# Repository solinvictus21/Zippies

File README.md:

# Zippies

Zippies are a project developed to create tiny, open source robots capable of following predefined path routines at high velocity in tight coordination together.

This repository includes all the details you need to build and run a Zippy...

- A complete set of [3D models](BodyModels) created in [SketchUp](https://www.sketchup.com/) that are required to build the outer body of a Zippy. Each of these parts is intended to be printed on a 3D printer and has been exported to a set of [STL files](BodyModels/STL) for convenience.
- A [schematic](LighthouseCircuit) and [complete bill of materials]() for a circuit designed to sense IR signals from a single HTC Vive Lighthouse to enable highly accurate, sub-millimeter localized positioning and orientation. The circuit is built in [AutoDesk Eagle](https://www.autodesk.com/products/eagle/free-download) and the PCB is available for immediate purchase directly [from Osh Park]().
- A complete [list of the additional hardware required](Documentation/Hardware.md) to assemble a Zippy. 
- The [software](PlatformIO) required to enable your Zippy robot to follow any predefined path you wish to create. A sample path is included in the codebase for testing new Zippy builds.
- An [iPhone app](iOSClient) (work in progress) that will allow you to control the Zippy directly and aid in debugging over Bluetooth.
- A [path building app](Builder) (work in progress) using [Unity 3D]() designed to allow you to build and simulate routines for your Zippies to follow and, on supported platforms, allow you to upload them directly to the Zippy via Bluetooth LE for immediate testing.

See each of the links above for more details about each aspect of this project and feel free to contact me for any assistance you may need if you are interested in building your own Zippy.

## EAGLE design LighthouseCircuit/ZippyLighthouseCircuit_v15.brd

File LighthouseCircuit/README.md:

# Lighthouse Sensor Circuit

This circuit is designed to provide sensors that detect IR signals from the HTC Vive Lighthouse in order to provide localized positioning for the Zippy. The board layout is published on [Osh Park](https://oshpark.com/shared_projects/vZVPRIY6) for easy ordering. All you have to do is solder the components onto it. The BOM and links to Digikey components are provided below.

1. 2x [BP104-FASZ](https://www.digikey.com/product-detail/en/osram-opto-semiconductors-inc/BP-104-FAS-Z/475-1344-1-ND/1227850) These are the IR sensors, the eyes of the circuit
2. 1x [TLV2464ID](https://www.digikey.com/product-detail/en/texas-instruments/TLV2464ID/296-10608-5-ND/380874) The heart of the circuit: a fast and reliable quad op-amp from TI.
3. First phase: voltage divider.
  - 2x [27k resistors](https://www.digikey.com/product-detail/en/panasonic-electronic-components/ERJ-3EKF2702V/P27.0KHCT-ND/1746753)
  - 2x [100nF capacictors](https://www.digikey.com/product-detail/en/samsung-electro-mechanics/CL10B104JB8NNNC/1276-1033-1-ND/3889119)
4. Second phase: transimpedance amplification
  - 2x [2.2pF capacitcors](https://www.digikey.com/product-detail/en/samsung-electro-mechanics/CL10C2R2BB8NNNC/1276-1084-1-ND/3889170)
  - 4x [100k resistors](https://www.digikey.com/product-detail/en/panasonic-electronic-components/ERJ-PA3J104V/P100KBZCT-ND/5036238) Also used in fourth-phase inverting amplification.
5. Third phase: high-pass filter.
  - 2x [4.7nf capacitors](https://www.digikey.com/product-detail/en/samsung-electro-mechanics/CL10B472JB8NNNC/1276-2061-1-ND/3890147)
  - 2x [18k resistors](https://www.digikey.com/product-detail/en/panasonic-electronic-components/ERJ-3EKF1802V/P18.0KHCT-ND/1746738)
6. Fourth phase: inverting amplification
  - 2x [1k resistors](https://www.digikey.com/product-detail/en/panasonic-electronic-components/ERJ-PB3D1001V/P20283CT-ND/6214538)

The passives can be soldered onto the board in any orientation, but pay particular attention to the orientation of the op-amp and diodes. Schematic diagram follows below if you're not an Eagle user.

This is essentially a mash-up and a doubling of the circuit I originally started with from [Alex Shtuchkin's project](https://github.com/ashtuchkin/vive-diy-position-sensor) and [another circuit](https://trmm.net/Lighthouse) tweeted about by Alan Yates along with [some lessons I've learned about op-amps](http://www.radio-electronics.com/info/circuits/opamp_non_inverting/op_amp_non-inverting.php) along the way and a LOT of experimentation. At this point, the circuit seems to be fairly reliable across the range of distances that I experiment with.

For the curious, it has been suggested that, if you only have one Lighthouse, you must have three sensors to determine orientation along a 2D plane. Not true, actually. To do it with only two sensors, all you need to know is which sensor was hit first, which is exactly how this project determines orientation along the ground with only two sensors.

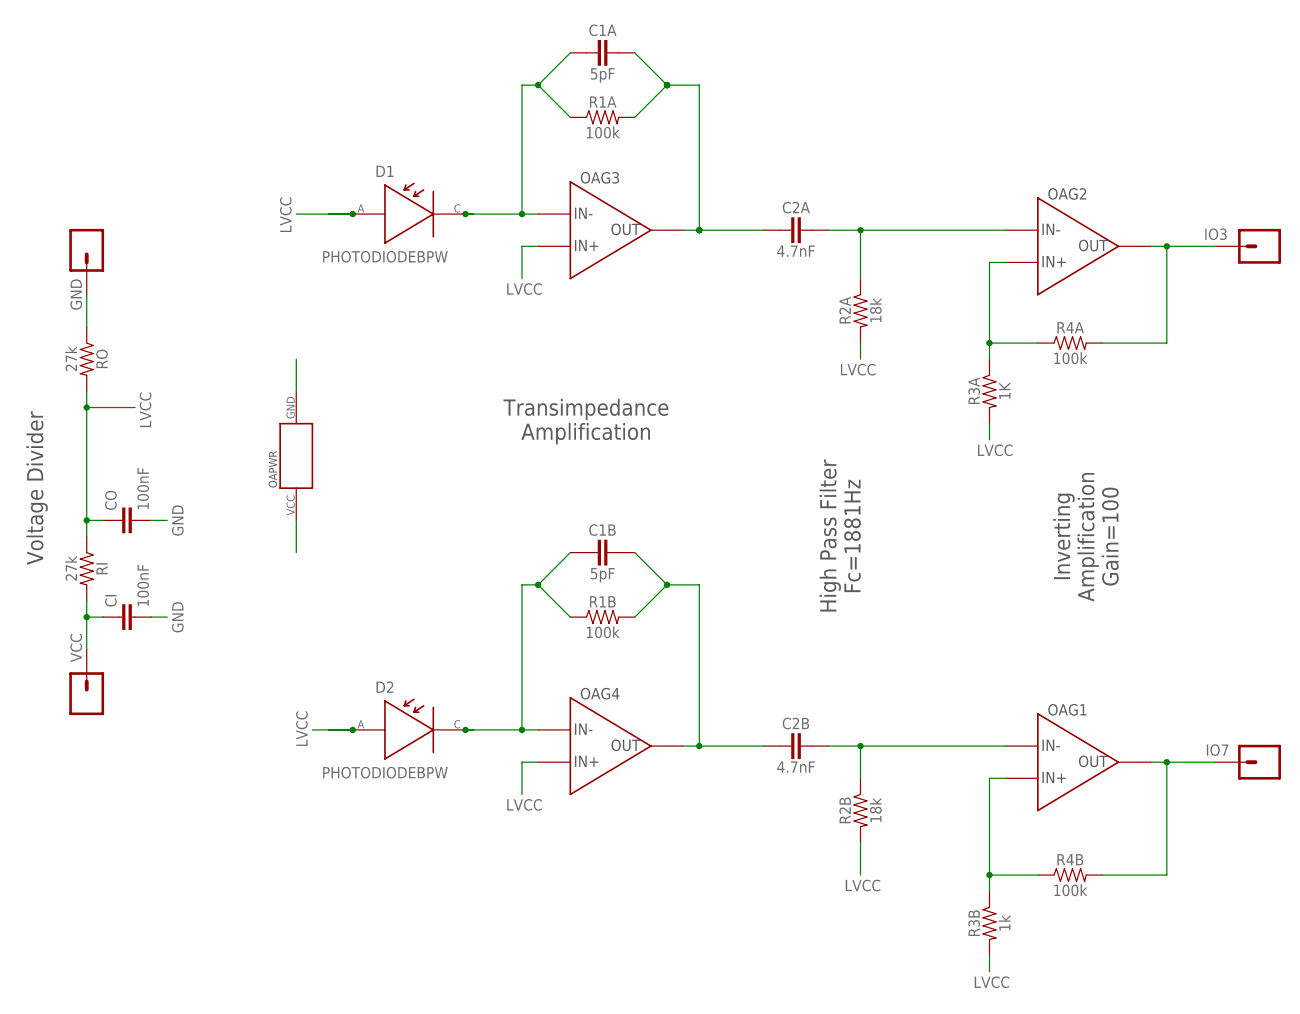
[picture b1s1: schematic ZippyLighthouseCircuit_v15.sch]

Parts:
C1A, C1B: 5pF; PASSIVE-0603
C2A, C2B: 4.7nF; PASSIVE-0603
CI: 100nF; 0603
CO: 100nF; 0603
D1, D2: PHOTODIODEBPW; BPW34_BP104_SMD
GND: CONN_01PTH_NO_SILK_YES_STOP; 1X01_NO_SILK
IO3, IO7: CONN_01PTH_NO_SILK_YES_STOP; 1X01_NO_SILK
OA: TLV2464IDM; D14-M
R1A, R1B, R4A, R4B: 100k; PASSIVE-0603
R2A, R2B: 18k; PASSIVE-0603
R3A: 1K; PASSIVE-0603
R3B: 1k; PASSIVE-0603
RI: 27k; 0603
RO: 27k; 0603
VCC: CONN_01PTH_NO_SILK_YES_STOP; 1X01_NO_SILK

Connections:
D1IN: C1B.1, D2.CATHODE, OA.13 (IN-), R1B.1
D1OA2P: C2B.2, OA.2 (IN-), R2B.1
D1OAOUT1: C1B.2, C2B.1, OA.14 (OUT), R1B.2
D2IN: C1A.1, D1.CATHODE, OA.9 (IN-), R1A.1
D2OA1OUT: C1A.2, C2A.1, OA.8 (OUT), R1A.2
D2OA2N: OA.5 (IN+), R3A.1, R4A.1
D2OA2P: C2A.2, OA.6 (IN-), R2A.1
GND: CI.2, CO.2, GND.1, OA.11 (GND), RO.1
IO3: IO3.1, OA.7 (OUT), R4A.2
IO7: IO7.1, OA.1 (OUT), R4B.2
LVCC: CO.1, D1.ANODE, D2.ANODE, OA.10 (IN+), OA.12 (IN+), R2A.2, R2B.2, R3A.2, R3B.2, RI.1, RO.2
unnamed: OA.3 (IN+), R3B.1, R4B.1
VCC: CI.1, OA.4 (VCC), RI.2, VCC.1

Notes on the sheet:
Voltage Divider
High Pass Filter Fc=1881Hz
Transimpedance Amplification
Inverting Amplification Gain=100

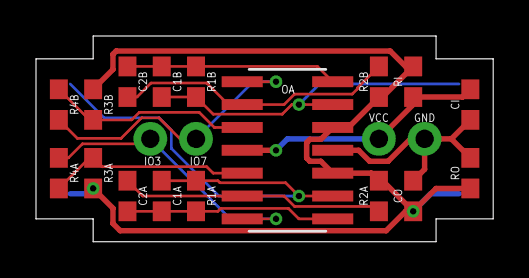
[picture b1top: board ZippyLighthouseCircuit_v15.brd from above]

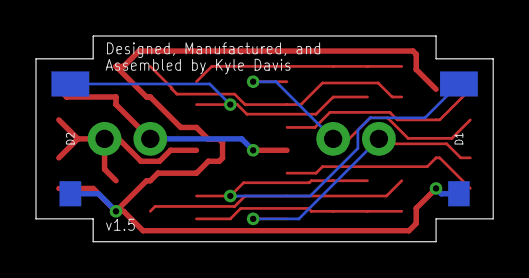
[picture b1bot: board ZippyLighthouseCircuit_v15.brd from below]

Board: 2 copper layers, 25.4 x 11.4 mm, 23 parts (2 on the bottom side), 13 nets.

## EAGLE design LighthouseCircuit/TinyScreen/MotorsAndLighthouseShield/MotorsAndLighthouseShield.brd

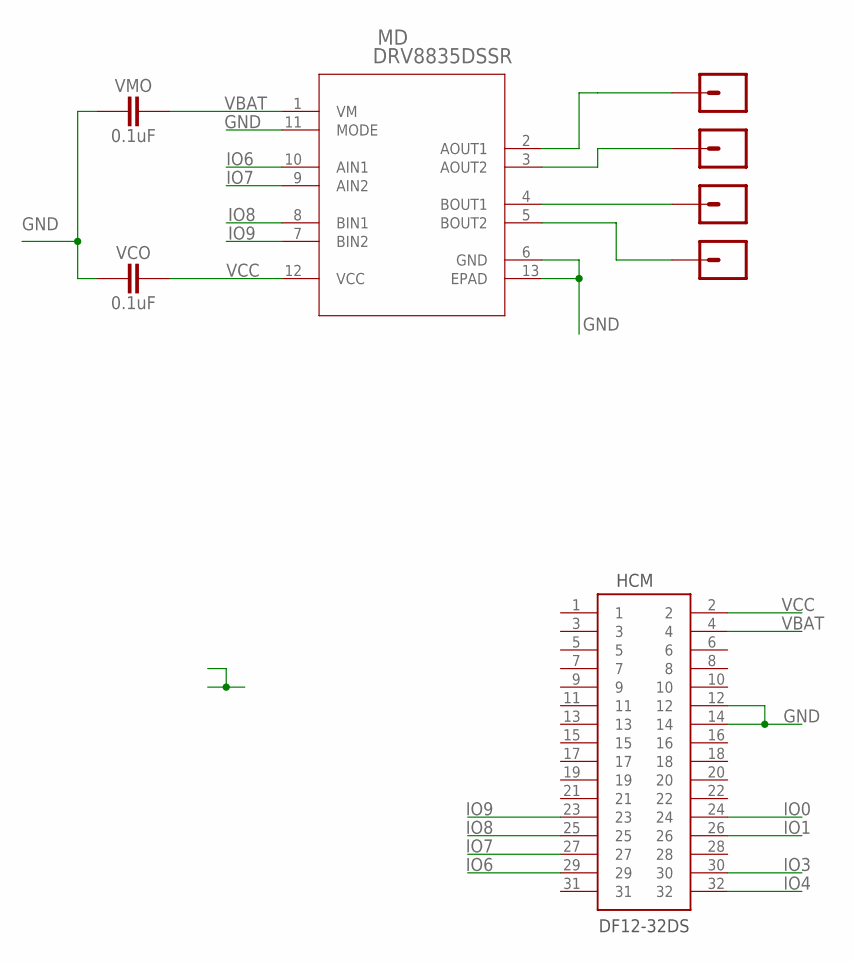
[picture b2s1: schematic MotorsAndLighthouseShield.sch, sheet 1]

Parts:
AO1, AO2: SINGLE-THROUGH-HOLE
B02: SINGLE-THROUGH-HOLE
BO1: SINGLE-THROUGH-HOLE
HCM: HIROSE-DF12-32DSMALE; DF12(3.0)-32DS-0.5V(86)-MALE
MD: DRV8835DSSR; DSS12_P9X2
VCO: 0.1uF; PASSIVE-0603
VMO: 0.1uF; PASSIVE-0603

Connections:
GND: HCM.12, HCM.14, MD.6 (GND), MD.11 (MODE), MD.13 (EPAD), VCO.1, VMO.1; also elsewhere on the board
IO0: HCM.24; also elsewhere on the board
IO1: HCM.26; also elsewhere on the board
IO3: HCM.30
IO4: HCM.32
IO6: HCM.29, MD.10 (AIN1)
IO7: HCM.27, MD.9 (AIN2)
IO8: HCM.25, MD.8 (BIN1)
IO9: HCM.23, MD.7 (BIN2)
unnamed: BO1.1, MD.2 (AOUT1)
unnamed: B02.1, MD.3 (AOUT2)
unnamed: AO1.1, MD.4 (BOUT1)
unnamed: AO2.1, MD.5 (BOUT2)
VBAT: HCM.4, MD.1 (VM), VMO.2
VCC: HCM.2, MD.12 (VCC), VCO.2; also elsewhere on the board

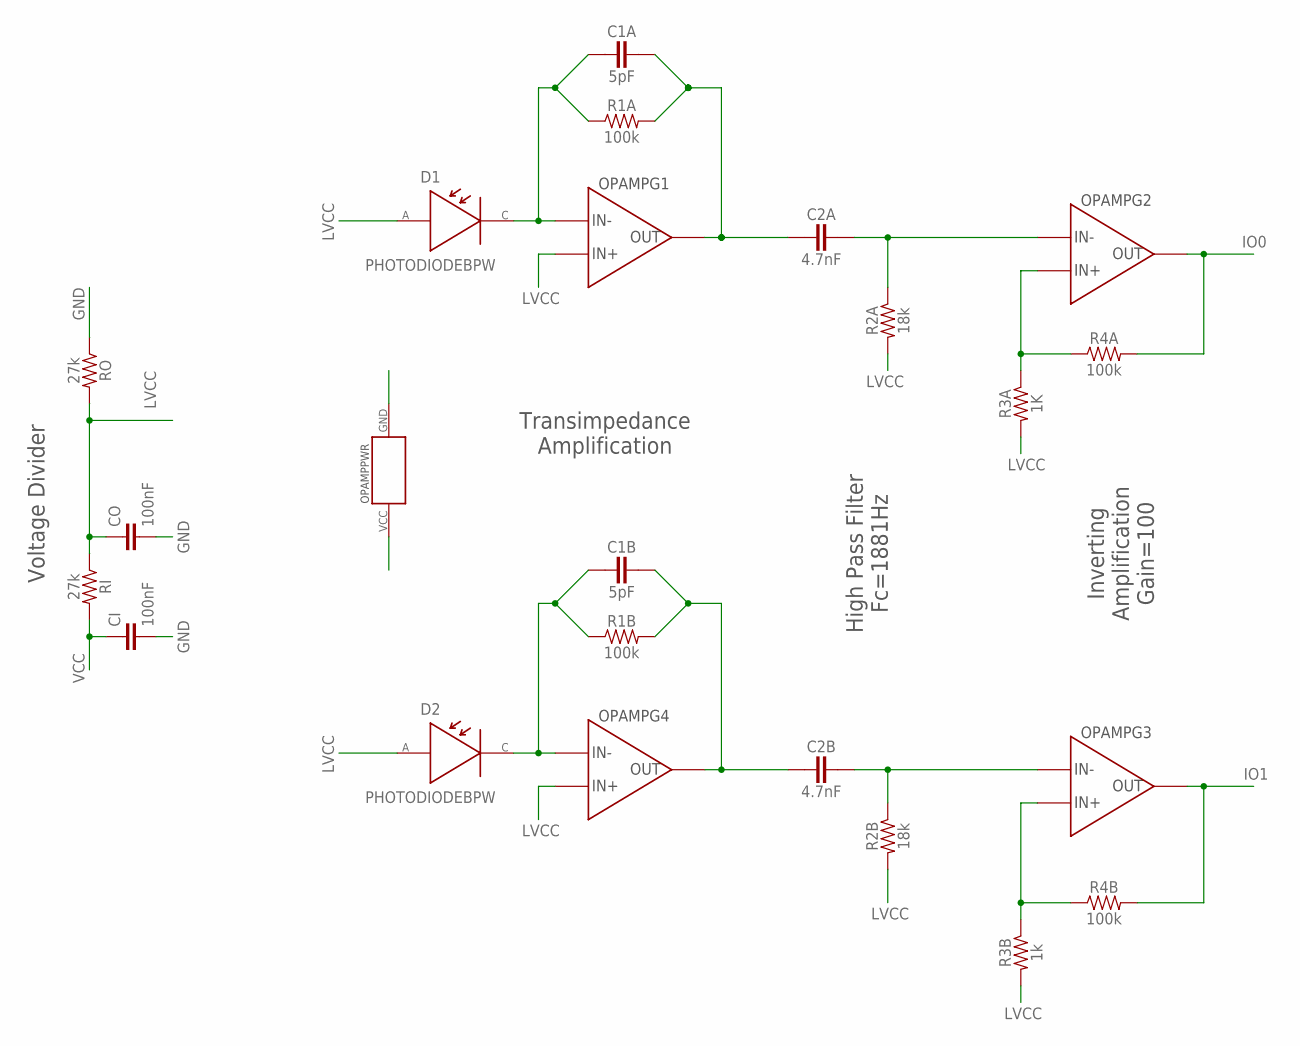
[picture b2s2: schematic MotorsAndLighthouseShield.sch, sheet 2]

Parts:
C1A, C1B: 5pF; PASSIVE-0603
C2A, C2B: 4.7nF; PASSIVE-0603
CI: 100nF; 0603
CO: 100nF; 0603
D1, D2: PHOTODIODEBPW; BPW34_BP104_SMD
OPAMP: TLV2464IPW; PW14
R1A, R1B, R4A, R4B: 100k; PASSIVE-0603
R2A, R2B: 18k; PASSIVE-0603
R3A: 1K; PASSIVE-0603
R3B: 1k; PASSIVE-0603
RI: 27k; 0603
RO: 27k; 0603

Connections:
D1IN1: C1B.1, D2.CATHODE, OPAMP.13 (IN-), R1B.1
D1OA2P1: C2B.2, OPAMP.9 (IN-), R2B.1
D1OAOUT2: C1B.2, C2B.1, OPAMP.14 (OUT), R1B.2
D2IN1: C1A.1, D1.CATHODE, OPAMP.2 (IN-), R1A.1
D2OA1OUT1: C1A.2, C2A.1, OPAMP.1 (OUT), R1A.2
D2OA2N1: OPAMP.5 (IN+), R3A.1, R4A.1
D2OA2P1: C2A.2, OPAMP.6 (IN-), R2A.1
GND: CI.2, CO.2, OPAMP.11 (GND), RO.1; also elsewhere on the board
IO0: OPAMP.7 (OUT), R4A.2; also elsewhere on the board
IO1: OPAMP.8 (OUT), R4B.2; also elsewhere on the board
LVCC: CO.1, D1.ANODE, D2.ANODE, OPAMP.3 (IN+), OPAMP.12 (IN+), R2A.2, R2B.2, R3A.2, R3B.2, RI.1, RO.2
unnamed: OPAMP.10 (IN+), R3B.1, R4B.1
VCC: CI.1, OPAMP.4 (VCC), RI.2; also elsewhere on the board

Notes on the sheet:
Voltage Divider
High Pass Filter Fc=1881Hz
Transimpedance Amplification
Inverting Amplification Gain=100

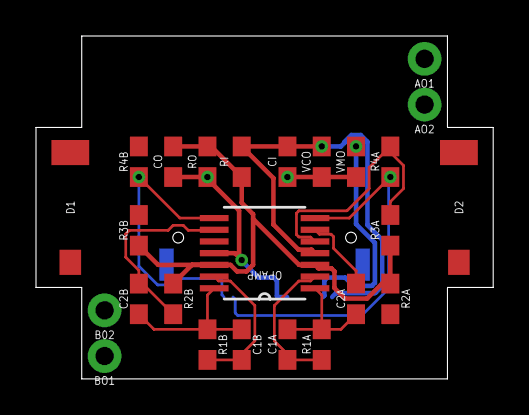
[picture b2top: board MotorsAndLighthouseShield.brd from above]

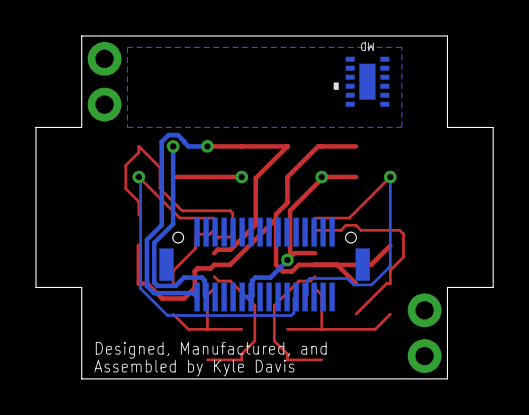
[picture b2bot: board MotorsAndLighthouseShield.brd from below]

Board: 2 copper layers, 25.4 x 19.1 mm, 27 parts (2 on the bottom side), 22 nets.

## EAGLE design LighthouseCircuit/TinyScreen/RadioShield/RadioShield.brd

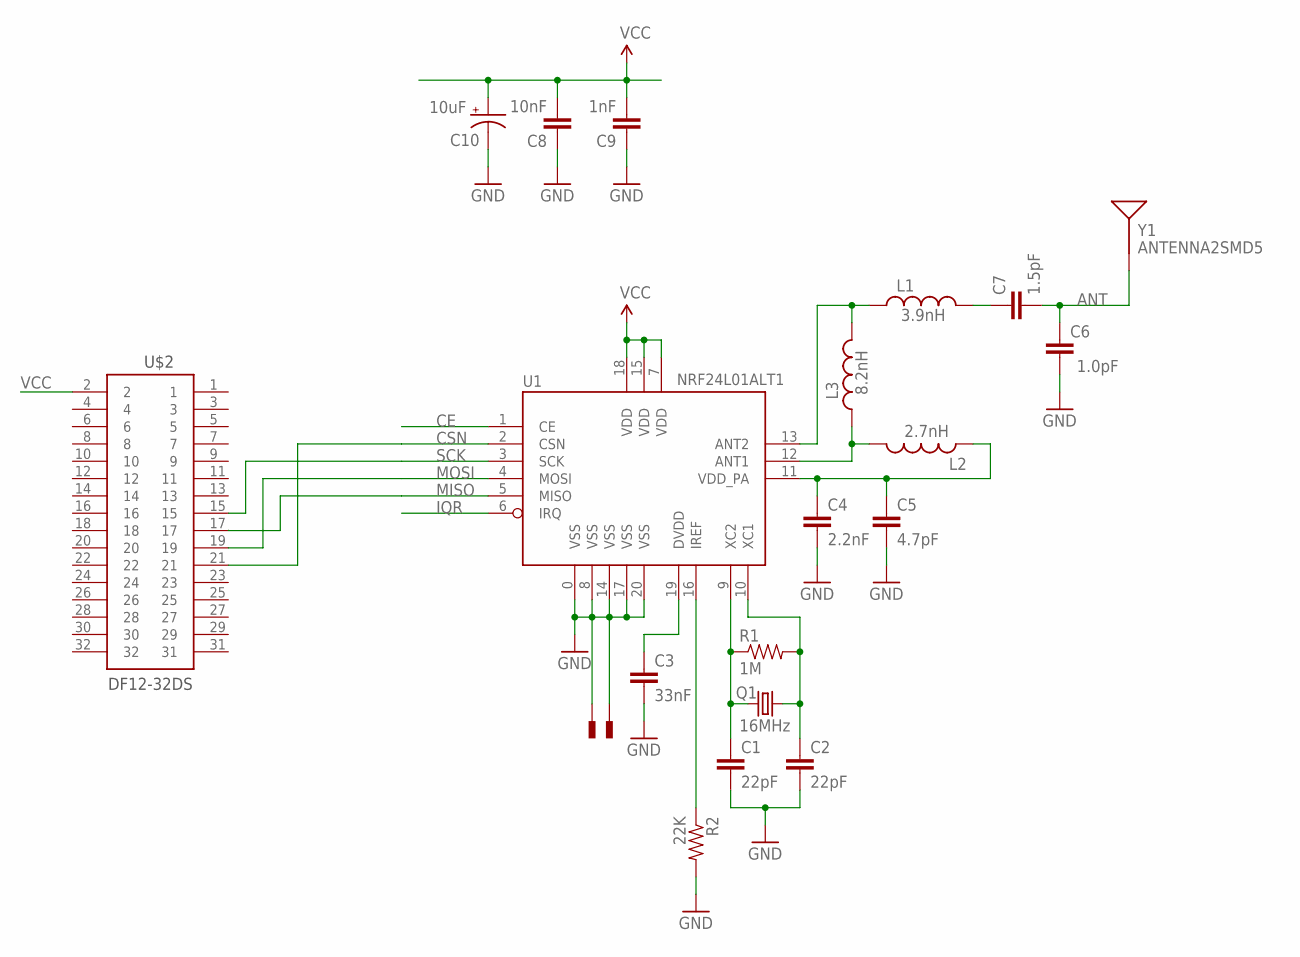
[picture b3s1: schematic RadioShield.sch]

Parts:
C1, C2: 22pF; 0402-CAP
C3: 33nF; 0402-CAP
C4: 2.2nF; 0402-CAP
C5: 4.7pF; 0402-CAP
C6: 1.0pF; 0402-CAP
C7: 1.5pF; 0402-CAP
C8: 10nF; 0402-CAP
C9: 1nF; 0402-CAP
C10: 10uF; EIA3216
L1: 3.9nH; C0402
L2: 2.7nH; C0402
L3: 8.2nH; C0402
Q1: 16MHz; CRYSTAL-SMD-5X3
R1: 1M; 0402-RES
R2: 22K; 0402-RES
U1: NRF24L01ALT1; QFN20_ALT1
U$1, U$4: PAD; PAD-0.008
U$2: HIROSE-DF12-32DSMALE; DF12(3.0)-32DS-0.5V(86)-MALE
Y1: ANTENNA2SMD5; ANTENNA-CHIP5

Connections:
ANT: C6.2, C7.2, Y1.FEED
CE: U1.1 (CE)
CSN: U1.2 (CSN), U$2.21
GND: C1.2, C2.2, C3.2, C4.2, C5.2, C6.1, C8.1, C9.1, C10.C (-), R2.2, U1.0 (VSS), U1.8 (VSS), U1.14 (VSS), U1.17 (VSS), U1.20 (VSS), U$1.P$1, U$4.P$1
IQR: U1.6 (IRQ)
MISO: U1.5 (MISO), U$2.17
MOSI: U1.4 (MOSI), U$2.19
unnamed: C1.1, Q1.1, R1.1, U1.9 (XC2)
unnamed: C2.1, Q1.3 (2), R1.2, U1.10 (XC1)
unnamed: L2.2, L3.1, U1.12 (ANT1)
unnamed: R2.1, U1.16 (IREF)
unnamed: C3.1, U1.19 (DVDD)
unnamed: L1.1, L3.2, U1.13 (ANT2)
unnamed: C4.1, C5.1, L2.1, U1.11 (VDD_PA)
unnamed: C7.1, L1.2
SCK: U1.3 (SCK), U$2.15
VCC: C8.2, C9.2, C10.A (+), U1.7 (VDD), U1.15 (VDD), U1.18 (VDD), U$2.2

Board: 2 copper layers, 21 parts (1 on the bottom side), 15 nets, no tracks yet.

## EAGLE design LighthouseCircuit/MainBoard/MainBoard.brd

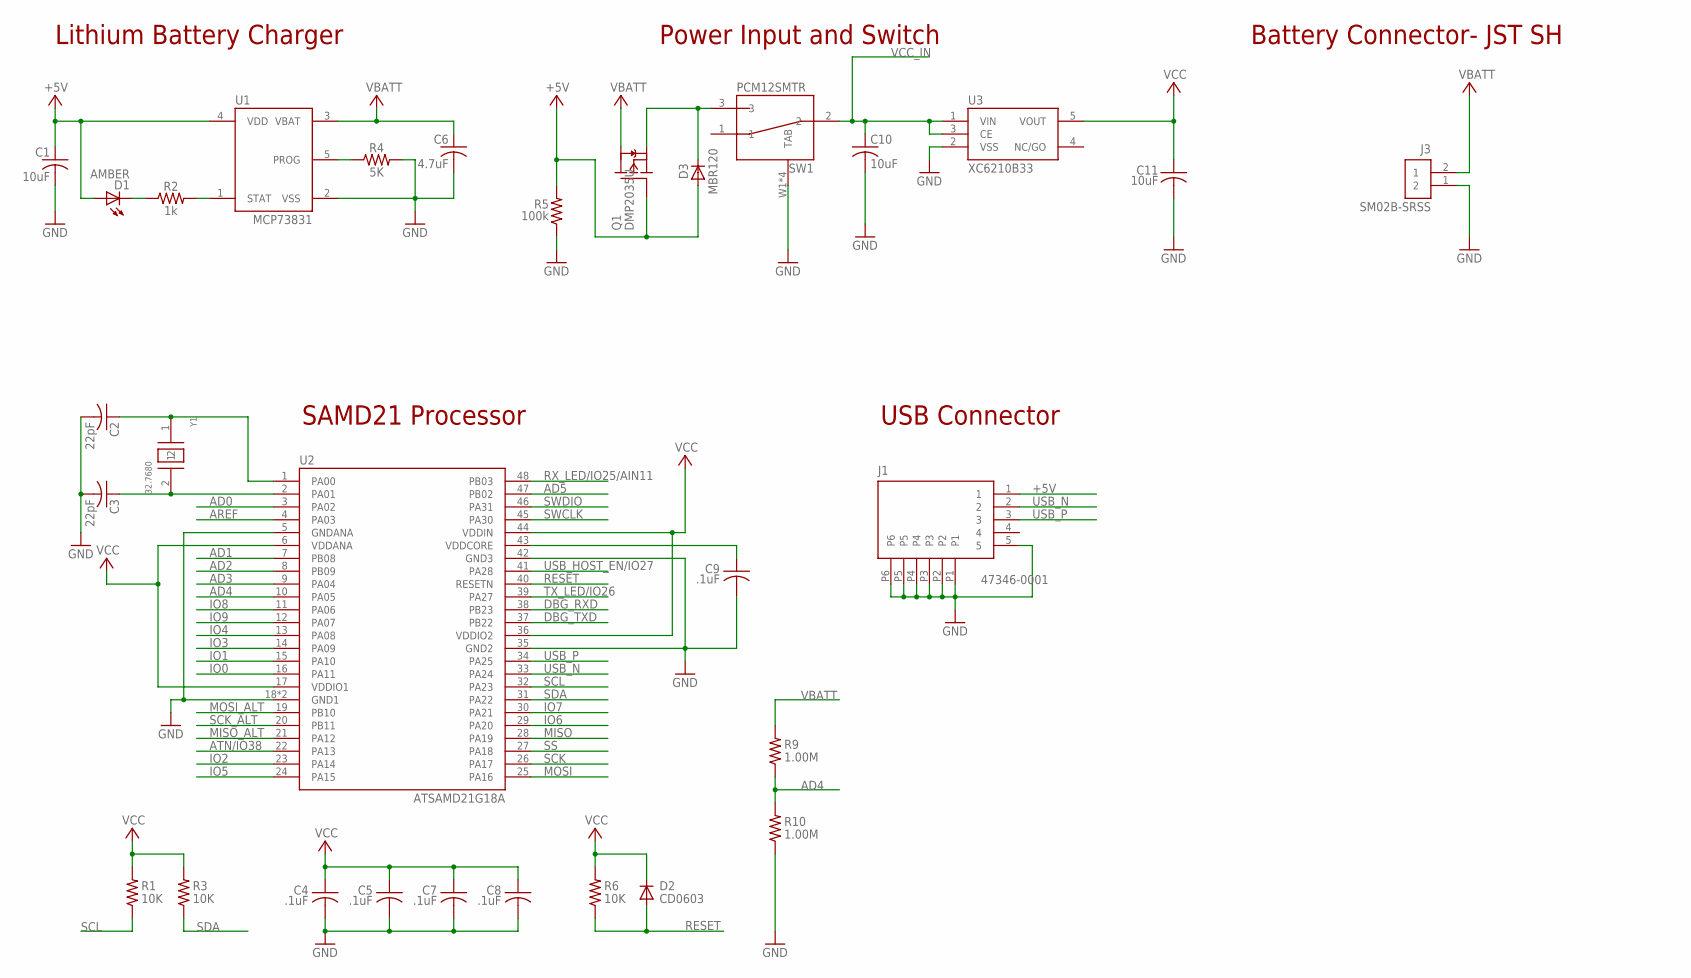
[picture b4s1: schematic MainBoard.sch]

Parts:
C1, C11: 10uF; C0603; PARTNO AS-ITM-00002
C2, C3: 22pF; C0402; PARTNO AS-ITM-00211
C4, C5, C7, C8, C9: .1uF; C0402; PARTNO AS-ITM-00008
C6: 4.7uF; C0603; PARTNO AS-ITM-00088
C10: 10uF; C0805; PARTNO AS-ITM-00045
D1: AMBER; LNJ_LED; PARTNO AS-ITM-00026
D2: CD0603; 0603; PARTNO AS-ITM-00009
D3: MBR120; SOD-123FL
J1: 47346-0001; MICRO_USB
J3: SM02B-SRSS; JST_SH_2X1
Q1: DMP2035U; SOT23
R1, R3, R6: 10K; 0402; PARTNO AS-ITM-00032
R2: 1k; 0402; PARTNO AS-ITM-00003
R4: 5K; 0402
R5: 100k; 0402; PARTNO AS-ITM-00004
R9, R10: 1.00M; 0402; PARTNO AS-ITM-00005
SW1: PCM12SMTR
U1: MCP73831; SOT-23
U2: ATSAMD21G18A; QFN48; PARTNO AS-ITM-00273
U3: XC6210B33; SOT-25
Y1: 32.7680; ABS06; PARTNO AS-ITM-00279

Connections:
+5V: C1.1, D1.A, D3.A, J1.1, Q1.B (G), R5.2, U1.4 (VDD)
AD0: U2.3 (PA02)
AD1: U2.7 (PB08)
AD2: U2.8 (PB09)
AD3: U2.9 (PA04)
AD4: R9.1, R10.2, U2.10 (PA05)
AD5: U2.47 (PB02)
AREF: U2.4 (PA03)
ATN/IO38: U2.22 (PA13)
DBG_RXD: U2.38 (PB23)
DBG_TXD: U2.37 (PB22)
GND: C1.2, C2.2, C3.2, C4.2, C5.2, C6.2, C7.2, C8.2, C9.2, C10.2, C11.2, J1.5, J1.P1, J1.P2, J1.P3, J1.P4, J1.P5, J1.P6, J3.1 (2), R4.2, R5.1, R10.1, SW1.W1 (TAB), SW1.W2 (TAB), SW1.W3 (TAB), SW1.W4 (TAB), U1.2 (VSS), U2.5 (GNDANA), U2.18 (GND1), U2.35 (GND2), U2.42 (GND3), U2.EXP (GND1), U3.2 (VSS)
IO0: U2.16 (PA11)
IO1: U2.15 (PA10)
IO2: U2.23 (PA14)
IO3: U2.14 (PA09)
IO4: U2.13 (PA08)
IO5: U2.24 (PA15)
IO6: U2.29 (PA20)
IO7: U2.30 (PA21)
IO8: U2.11 (PA06)
IO9: U2.12 (PA07)
MISO: U2.28 (PA19)
MISO_ALT: U2.21 (PA12)
MOSI: U2.25 (PA16)
MOSI_ALT: U2.19 (PB10)
unnamed: C2.1, U2.1 (PA00), Y1.1
unnamed: D3.C, Q1.E (S), SW1.3
unnamed: C3.1, U2.2 (PA01), Y1.2
unnamed: D1.C, R2.1
unnamed: R4.1, U1.5 (PROG)
unnamed: R2.2, U1.1 (STAT)
unnamed: C9.1, U2.43 (VDDCORE)
RESET: D2.A, R6.1, U2.40 (RESETN)
RX_LED/IO25/AIN11: U2.48 (PB03)
SCK: U2.26 (PA17)
SCK_ALT: U2.20 (PB11)
SCL: R1.1, U2.32 (PA23)
SDA: R3.1, U2.31 (PA22)
SS: U2.27 (PA18)
SWCLK: U2.45 (PA30)
SWDIO: U2.46 (PA31)
TX_LED/IO26: U2.39 (PA27)
USB_HOST_EN/IO27: U2.41 (PA28)
USB_N: J1.2, U2.33 (PA24)
USB_P: J1.3, U2.34 (PA25)
VBATT: C6.1, J3.2 (1), Q1.C (D), R9.2, U1.3 (VBAT)
VCC: C4.1, C5.1, C7.1, C8.1, C11.1, D2.C, R1.2, R3.2, R6.2, U2.6 (VDDANA), U2.17 (VDDIO1), U2.36 (VDDIO2), U2.44 (VDDIN), U3.5 (VOUT)
VCC_IN: C10.1, SW1.2, U3.1 (VIN), U3.3 (CE)

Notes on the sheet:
SAMD21 Processor
Power Input and Switch
Lithium Battery Charger
Battery Connector- JST SH
USB Connector

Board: 2 copper layers, 30 parts (0 on the bottom side), 18 nets, no tracks yet.

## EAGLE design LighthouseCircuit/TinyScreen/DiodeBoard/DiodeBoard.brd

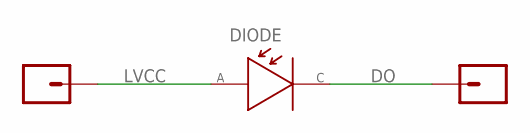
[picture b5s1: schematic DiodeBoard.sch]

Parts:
DI: SINGLE-THROUGH-HOLE
DIODE: PHOTODIODEBPW; BPW34_BP104_SMD
DO: SINGLE-THROUGH-HOLE

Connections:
DO: DIODE.CATHODE, DO.1
LVCC: DI.1, DIODE.ANODE

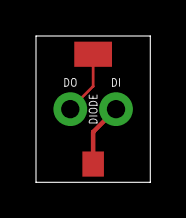
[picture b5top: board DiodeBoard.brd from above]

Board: 2 copper layers, 6.3 x 8.1 mm, 3 parts (0 on the bottom side), 2 nets.

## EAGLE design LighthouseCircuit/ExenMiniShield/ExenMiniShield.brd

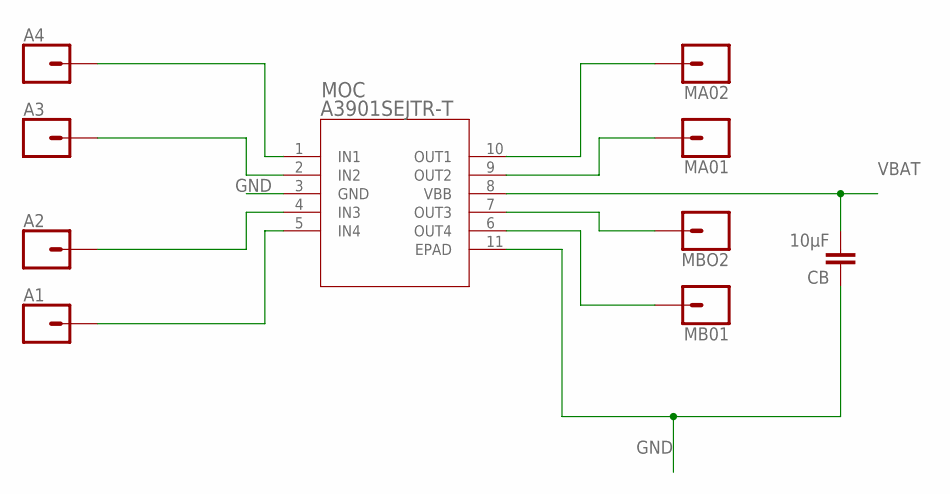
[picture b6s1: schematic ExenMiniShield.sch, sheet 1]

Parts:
A1, A2, A3, A4: CONN_01PTH_NO_SILK_YES_STOP; 1X01_NO_SILK
CB: 10μF; 0603
MA01, MA02: CONN_01PTH_NO_SILK_YES_STOP; 1X01_NO_SILK
MB01: CONN_01PTH_NO_SILK_YES_STOP; 1X01_NO_SILK
MBO2: CONN_01PTH_NO_SILK_YES_STOP; 1X01_NO_SILK
MOC: A3901SEJTR-T; DFN-10_DD

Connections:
GND: CB.1, MOC.3 (GND), MOC.11 (EPAD); also elsewhere on the board
MA01: MBO2.1, MOC.7 (OUT3)
MA02: MB01.1, MOC.6 (OUT4)
MB01: MA02.1, MOC.10 (OUT1)
MB02: MA01.1, MOC.9 (OUT2)
unnamed: A1.1, MOC.5 (IN4)
unnamed: A2.1, MOC.4 (IN3)
unnamed: A4.1, MOC.1 (IN1)
unnamed: A3.1, MOC.2 (IN2)
VBAT: CB.2, MOC.8 (VBB); also elsewhere on the board

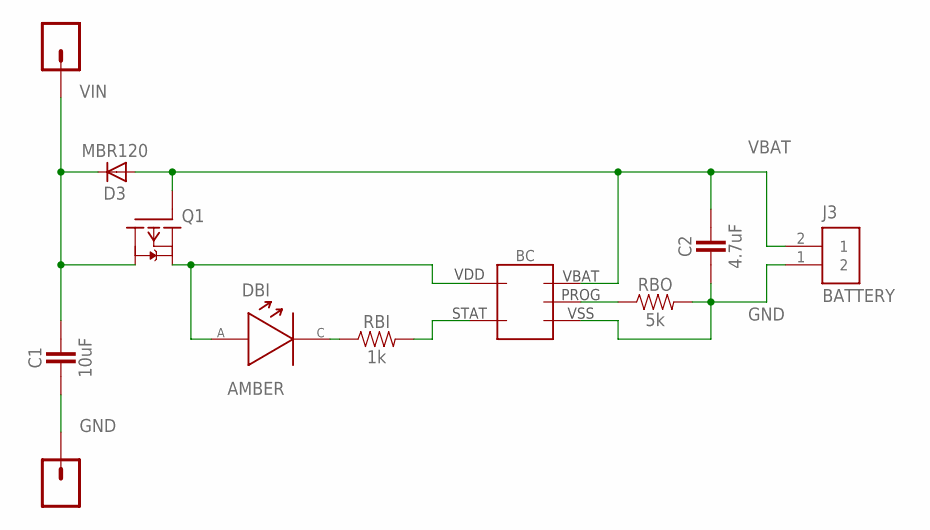
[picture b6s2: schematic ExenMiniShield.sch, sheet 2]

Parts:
BC: BATTERYCHARGER; SOT-753
C1: 10uF; PASSIVE-0603
C2: 4.7uF; PASSIVE-0603
D3: MBR120; SOD-123FL
DBI: AMBER; PASSIVE-0603
GND: CONN_01PTH_NO_SILK_YES_STOP; 1X01_NO_SILK
J3: BATTERY; JST_SH_2X1
Q1: DMP2035U; SOT23
RBI: 1k; PASSIVE-0603
RBO: 5k; PASSIVE-0603
VIN: CONN_01PTH_NO_SILK_YES_STOP; 1X01_NO_SILK

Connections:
GND: BC.VSS, C1.1, C2.1, GND.1, J3.1 (2), RBO.2; also elsewhere on the board
unnamed: DBI.2 (CATHODE), RBI.1
unnamed: BC.STAT, RBI.2
unnamed: BC.PROG, RBO.1
VBAT: BC.VBAT, C2.2, D3.A, J3.2 (1), Q1.B (G); also elsewhere on the board
VDD: BC.VDD, DBI.1 (ANODE), Q1.E (S)
VIN: C1.2, D3.C, Q1.C (D), VIN.1

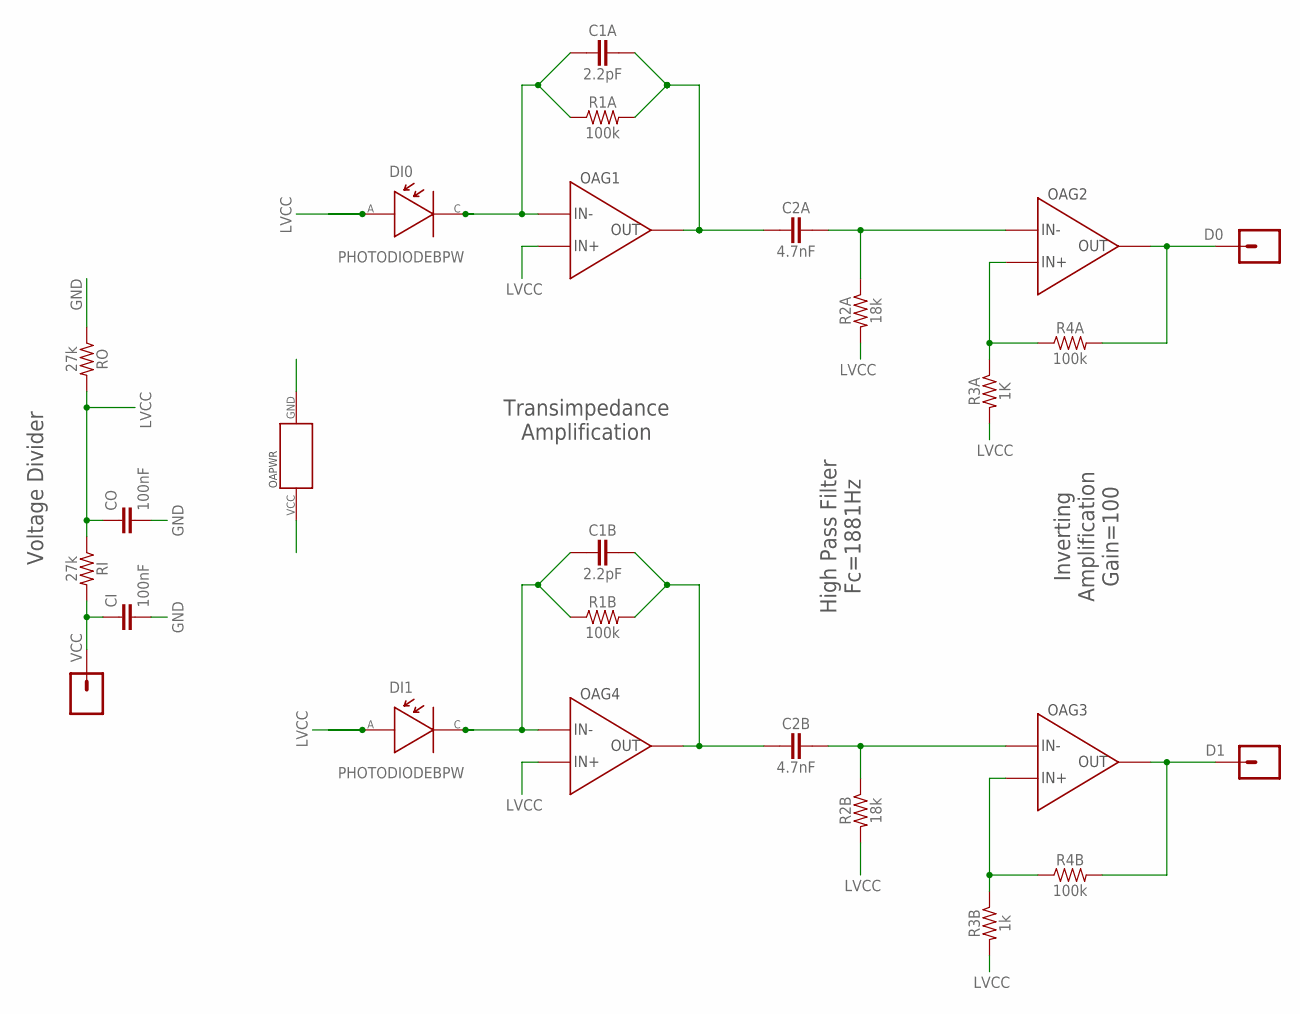
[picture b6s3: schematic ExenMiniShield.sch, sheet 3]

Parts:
C1A, C1B: 2.2pF; PASSIVE-0603
C2A, C2B: 4.7nF; PASSIVE-0603
CI: 100nF; 0603
CO: 100nF; 0603
D0, D1: CONN_01PTH_NO_SILK_YES_STOP; 1X01_NO_SILK
DI0, DI1: PHOTODIODEBPW; BPW34_BP104_SMD
OA: TLV2464IPW; PW14
R1A, R1B, R4A, R4B: 100k; PASSIVE-0603
R2A, R2B: 18k; PASSIVE-0603
R3A: 1K; PASSIVE-0603
R3B: 1k; PASSIVE-0603
RI: 27k; 0603
RO: 27k; 0603
VCC: CONN_01PTH_NO_SILK_YES_STOP; 1X01_NO_SILK

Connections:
D0: D0.1, OA.7 (OUT), R4A.2
D1: D1.1, OA.8 (OUT), R4B.2
D1IN: C1B.1, DI1.CATHODE, OA.13 (IN-), R1B.1
D1OA2P: C2B.2, OA.9 (IN-), R2B.1
D1OAOUT1: C1B.2, C2B.1, OA.14 (OUT), R1B.2
D2IN: C1A.1, DI0.CATHODE, OA.2 (IN-), R1A.1
D2OA1OUT: C1A.2, C2A.1, OA.1 (OUT), R1A.2
D2OA2N: OA.5 (IN+), R3A.1, R4A.1
D2OA2P: C2A.2, OA.6 (IN-), R2A.1
GND: CI.2, CO.2, OA.11 (GND), RO.1; also elsewhere on the board
LVCC: CO.1, DI0.ANODE, DI1.ANODE, OA.3 (IN+), OA.12 (IN+), R2A.2, R2B.2, R3A.2, R3B.2, RI.1, RO.2
unnamed: OA.10 (IN+), R3B.1, R4B.1
VCC: CI.1, OA.4 (VCC), RI.2, VCC.1

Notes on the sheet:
Voltage Divider
High Pass Filter Fc=1881Hz
Transimpedance Amplification
Inverting Amplification Gain=100

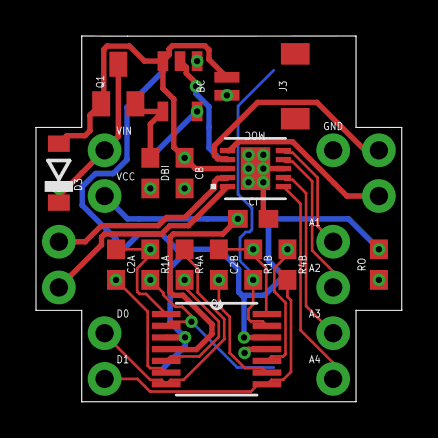
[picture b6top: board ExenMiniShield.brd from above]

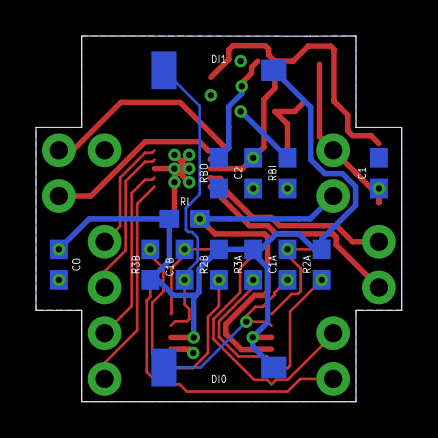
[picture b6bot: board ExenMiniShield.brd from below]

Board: 2 copper layers, 20.3 x 20.3 mm, 43 parts (14 on the bottom side), 27 nets.

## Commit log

2018-03-02 First check-in of source code.
2018-03-02 Added 3D models for body assembly.
2018-03-02 Added schematic and board layout for HTC Vive Lighthouse circuit.
2018-03-02 Added Autodesk Eagle library required for HTC Vive Lighthouse circuit.
2018-03-02 Updated Arduino project.
2018-03-02 Added iOS client for debugging Zippies over Bluetooth.
2018-03-02 Clarified comment about how the orientation vector is calculated.
2018-03-05 Renamed Arduino project to remove '+' symbol. Updated PID controller to be a little more accurate.
2018-04-04 Preparing for minor Lighthouse tracking refactor.
2018-04-16 Preparing to enhance path-following algorithm.
2018-04-18 Now have a working PID model. Refactoring MoveTowardPoint into FollowPath to accept multiple points.
2018-04-19 Finally got the PID control ironed out. They will now smoothly follow a demo elliptical path in area of about 2 meters across and 1.5 meters in depth all on their own.
2018-04-19 Tweaked the Kp of the PIDs up a notch.
2018-04-25 Further progress toward stabilizing the Lighthouse detection.
2018-04-27 Zippy now moves smoothly in a figure 8 around the center of where the Lighthouse is pointing. Next step will be to add tight coordination of more than one Zippy.
2018-05-04 Modified 3D body models to use offset, direct-drive wheels because the gears were too small to be printed accurately enough to prevent binding and other movement errors that prevented accurate self-n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
2018-05-08 As the self-driving control model has become more refined, I've been able to push the Zippies faster. Now set at a max velocity of 800mm/s.
2018-05-09 Further refined the driving model and improved the position data by incorporating factory calibration data into the position calculation based on code and documentation from the libsurvive project. T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
2018-05-24 Significantly stabilized the acceleration from full stop by slowing down the maximum speed. There is a physical limitation preventing them from accelerating any faster from full stop. Now that their 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
2018-05-30 Moved to separate PID configuration for each wheel. Since the left wheel is offset toward the rear and the right wheel is offset toward the front, the left wheel needs to be less aggressive or the Zi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
2018-07-12 Reached a point where auto-drive mode is consistent and reliable.
2018-07-26 Path following is now very smooth. Zippies sync up on Lighthouse OOTX frame preamble (17 successive zero OOTX bits). Added config to modify behavior of different Zippies. Started work on using Blueto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
2018-08-01 Zippies can now perform perfectly synchronous drive along any predefined path.
2018-08-16 Tagged model in each SketckUp file that should be used as the current model to 3D print.
2018-08-17 Added an integrated motor/lighthouse circuit design and updated path following code to use bezier curves to make path following significantly smoother.
2018-08-28 Working on creating individual commands and implementing arbitrary path-following of straight line segments as well as bezier curves.
2018-10-02 Beginning to transition PID model from linear+angular velocity PIDs to independent PIDs for each wheel.
2018-11-08 Implemented two different models for kinematics. Experimenting with each to determine which is more reliable across the widest range of velocities.
2018-12-03 Further refinement of smooth movement across a wider variety of velocities.
2019-02-27 Preparing to merge codebase changes from separate project.
2019-03-01 Significantly stabilized the position calculation and the new driving model with independent PIDs for each wheel.
2019-04-19 Progress toward using bi-arc computations for execution of path following.
2019-06-18 Added support for bi-arc movement, which can be more easily linearly interpolated than cubic bezier movement. Made several other architectural changes to streamline movement planning.
2019-06-26 Moving away from pure pursuit and exploring other path execution algorithms.
2019-06-27 Minor changed to SketchUp models.
2019-07-29 Moving toward use of a matrix for 2D rotations.
2019-08-23 Numerous improvements to movement algorithm, path planning, and dance routine execution.
2019-11-01 Significantly refactored the sensor fusion to calculate updated positions in lock-step with the Lighthouse sweeps. New positions are now calculated only after both sensors have received a hit on both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
2019-11-26 Eliminated use of routine controller and simplified the model for defining paths while adding support for velocity easing for each path segment.
2019-12-27 Working on initial demo of multiple Zippies in coordination.
2020-02-01 Made some huge strides in these changes. Nothing is quite as satisfying as deleting code, and I've deleted much code in this commit, because I've been able to develop a new path-following algorithm t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
2020-04-08 Significant changes and refactored codebase layout. Improvements made to path following, PID control, path execution, added a new default path, and many other changes.
2020-07-02 Switched path definitions to use monotonic hermite curves, allowing for significantly more sophisticated and flexible path planning.
2020-07-22 Working on a new path following implementation.
2020-07-24 Further progress on following.
2020-12-09 Attempting to perfect path following controller code. Preparing to delete old path definition code.
2021-04-29 Further exploration of path-following algorithms.
2021-07-06 Switching to a kinematic movement model instead of using cubic beziers for path planning.
2021-11-30 Preparing to prune old code out of the codebase.
2021-11-30 Pruned out some old code. Continuing to prune out further.
2021-11-30 Further pruning of old code.
2023-02-13 Checkpoint where we are beginning to get Zippies to execute full reoutines.
2023-08-23 Checkpoint prior to use of Webots to debug and optimize path-following code.
2023-08-28 Ported over fixes and enhancements to driving algorithms from Webots simulation experiments. Added a motor tuning controller to begin work setting up tests to capture motor tuning parameters to bette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
2023-09-07 Further optimization of driving algorithms.
2024-07-18 Added support for remote control from the iPhone app via Bluetooth. Many other changes and optimizations. Still a WIP..

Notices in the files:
parts and their libraries:
SparkFun-Connectors: Licensing: Creative Commons ShareAlike 4.0 International - https://creativecommons.org/licenses/by-sa/4.0
